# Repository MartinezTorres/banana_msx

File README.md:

# banana_msx

Building module:

banana_msx/kernel/module$ make ARCH=arm CROSS_COMPILE=arm-linux-gnueabihf-

Building kernel:

make ARCH=arm CROSS_COMPILE=arm-linux-gnueabihf- menuconfig zImage modules dtbs -j 4

make modules_install INSTALL_MOD_PATH=tmp_install

sudo update-initramfs -c -v -k 5.15.93

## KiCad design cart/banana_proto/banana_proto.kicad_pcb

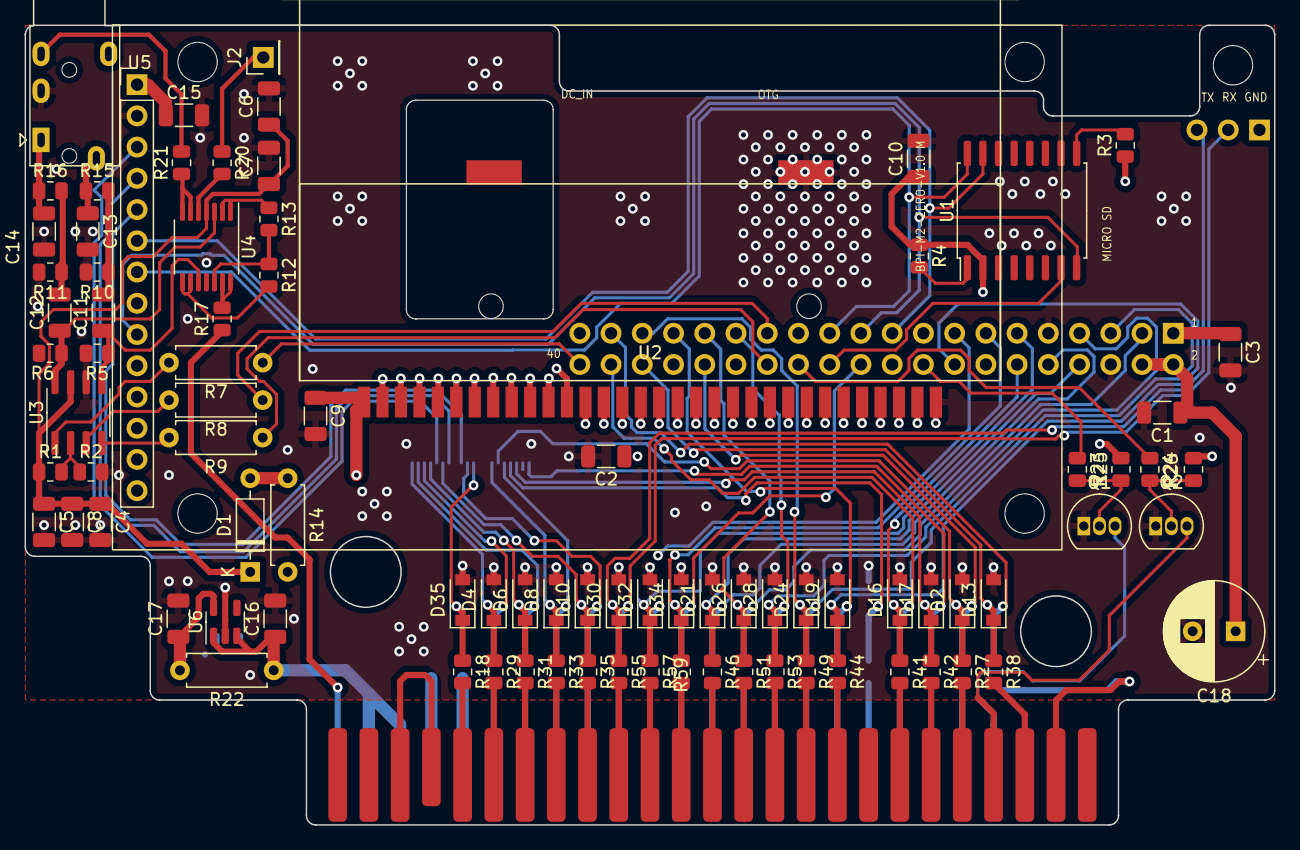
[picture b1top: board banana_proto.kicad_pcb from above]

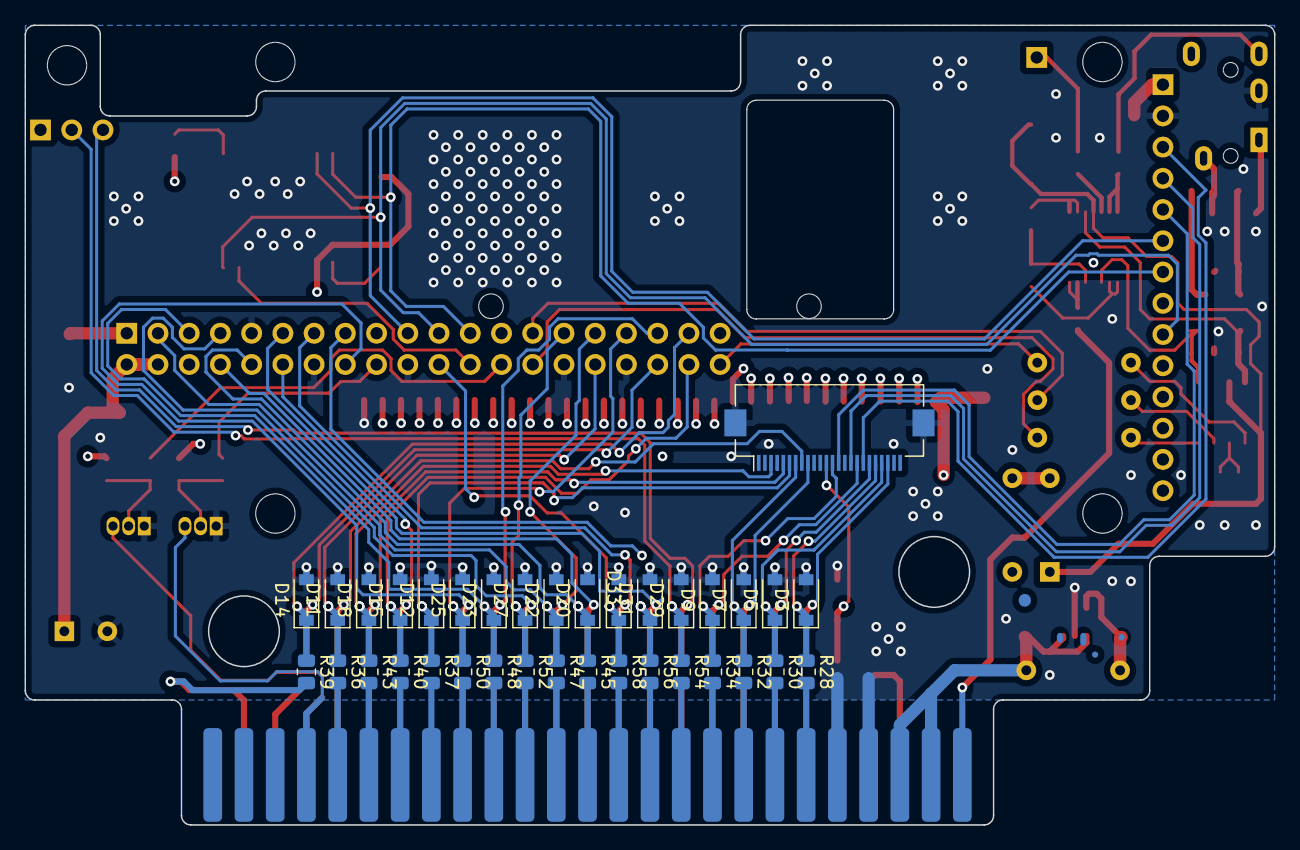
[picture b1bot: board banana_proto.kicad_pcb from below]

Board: 4 copper layers, 101.6 x 65.0 mm, 123 parts (34 on the bottom side), 112 nets.

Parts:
B1: Banana_PI_M2_Zero; BananaPI M2 Zero
BUS1: MSX_SLOT_EDGE-CON; msx_cartridge
C1, C2, C3, C5, C6, C9, C10, C15, C16, C17: 1uF; C_1206_3216Metric
C4: 10uF; C_1206_3216Metric
C7, C8: 0.1uF; C_1206_3216Metric
C11, C12: 3.3uF; C_1206_3216Metric
C13, C14: 10nF; C_1206_3216Metric
C18: 2200uF 6.3V; CP_Radial_D8.0mm_P3.50mm
D1: 1N6858; D_DO-35_SOD27_P7.62mm_Horizontal
D2, D3, D4, D5, D6, D7, D8, D9, D10, D11, D12, D13, D14, D15, D16, D17, D18, D19, D20, D21, D22, D23, D24, D25, D26, D27, D28, D29, D30, D31, D32, D33, D34, D35: BZT52C2V7-TP; D_SOD-123
J2: COMPOSITE; PinHeader_1x01_P2.54mm_Vertical
J3: AudioJack3_Ground; Jack_3.5mm_PJ320E_Horizontal
Q1, Q2: 2N3904; TO-92_Inline
R1, R2, R10, R11: 10k; R_0805_2012Metric
R3, R4, R18, R23, R24, R27, R28, R29, R30, R31, R32, R33, R34, R35, R36, R37, R38, R39, R40, R41, R42, R43, R44, R45, R46, R47, R48, R49, R50, R51, R52, R53, R54, R55, R56, R57, R58, R59: 330; R_0805_2012Metric
R5, R6: 267K; R_0805_2012Metric
R7, R8, R9, R14: 0; R_Axial_DIN0207_L6.3mm_D2.5mm_P7.62mm_Horizontal
R12, R13, R25, R26: 2K2; R_0805_2012Metric
R15, R16, R17: 560; R_0805_2012Metric
R20, R21: 75; R_0805_2012Metric
R22: 0 DNP; R_Axial_DIN0207_L6.3mm_D2.5mm_P7.62mm_Horizontal
U1: MT25QL01GBBB; SOIC-16W_7.5x10.3mm_P1.27mm
U2: CartBus; DSL_Cartridge_Reader
U3: CS4334; SOIC-8_3.9x4.9mm_P1.27mm
U4: MAX4395; TSSOP-14_4.4x5mm_P0.65mm
U5: ILI9341_TFT_LCD_Module; ILI9341 TFT LCD 24 modul
U6: NCP699SN50T1G; SOT-23-5

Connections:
+3V3: B1.P01 (VCC-3V3), B1.P17 (VCC-3V3), C2.1, C3.1, C10.1, C15.1, R3.1, R4.1, R25.2, R26.2, U1.2 (VCC), U5.1 (VCC), U5.8 (LCD_BACKGROUND)
+5V: B1.P02 (VCC-5V), B1.P04 (VCC-5V), C1.1, C9.1, C17.1, C18.1, R14.2, R22.2, U2.1 (VCC), U6.5 (OUT)
+5VA: C4.1, C5.1, C6.1, C7.1, C8.1, D1.1 (K), R1.1, U3.7 (VA), U4.4 (V+)
/A0: BUS1.28 (A0), R59.2
/A1: BUS1.27 (A1), R58.2
/A2: BUS1.30 (A2), R57.2
/A3: BUS1.29 (A3), R56.2
/A4: BUS1.32 (A4), R55.2
/A5: BUS1.31 (A5), R54.2
/A6: BUS1.22 (A6), R53.2
/A7: BUS1.21 (A7), R52.2
/A8: BUS1.24 (A8), R51.2
/A9: BUS1.17 (A9), R50.2
/A10: BUS1.20 (A10), R49.2
/A11: BUS1.19 (A11), R48.2
/A12: BUS1.23 (A12), R47.2
/A13: BUS1.26 (A13), R46.2
/A14: BUS1.25 (A14), R45.2
/A15: BUS1.18 (A15), R44.2
/COMPOSITE: J3.R2, R21.2
/D0: BUS1.34 (D0), R35.2
/D1: BUS1.33 (D1), R34.2
/D2: BUS1.36 (D2~), R33.2
/D3: BUS1.35 (D3), R32.2
/D4: BUS1.38 (D4), R31.2
/D5: BUS1.37 (D5), R30.2
/D6: BUS1.40 (D6), R29.2
/D7: BUS1.39 (D7), R28.2
/I2S_BCLK: B1.P27 (PA19), R8.1
/I2S_DOUT: B1.P40 (PA20), R7.1
/I2S_MCLK: B1.P28 (PA18), R9.1
/IRQ: B1.P26 (PC7), R24.1
/LCD_D/~C: B1.C14 (PE10), U5.5 (LCD_D/~C)
/LCD_~CS: B1.C18 (PE8), U5.3 (LCD_~CS)
/LCD_~RESET: B1.C16 (PE9), U5.4 (LCD_~RESET)
/SND: BUS1.49 (SOUNDOUT), R17.1
/SND_L_RAW: C12.1, R6.1, U3.8 (AOUTL), U4.3 (+)
/SND_R_RAW: C11.1, R5.1, U3.5 (AOUTR), U4.10 (+)
/SPI0_CLK: B1.P23 (PC2), U1.16 (SCK), U5.7 (LCD_SCK)
/SPI0_CS: B1.P24 (PC3), U1.7 (~CE)
/SPI0_MISO: B1.P21 (PC1), U1.8 (SO/IO1), U5.9 (LCD_MISO)
/SPI0_MOSI: B1.P19 (PC0), U1.15 (SI/IO0), U5.6 (LCD_MOSI)
/SPKR_L: C14.1, J3.T, R16.1
/SPKR_R: C13.1, J3.S, R15.1
/SW1: BUS1.44 (SW1), BUS1.46 (SW2)
/SYS_CLK: BUS1.42 (CLOCK), R18.2
/VIN: BUS1.45 (+5V), BUS1.47 (+5V), C16.1, R22.1, U6.1 (IN), U6.3 (EN)
/WAIT: B1.P18 (PC4), R23.1
/_A0: B1.P13 (PA0), D34.1 (K), R59.1
/_A1: B1.P22 (PA2), D33.1 (K), R58.1
/_A2: B1.P11 (PA1), D32.1 (K), R57.1
/_A3: B1.P15 (PA3), D31.1 (K), R56.1
/_A4: B1.S03 (PA4-TX), D30.1 (K), R55.1
/_A5: B1.S02 (PA5-RX), D29.1 (K), R54.1
/_A6: B1.P07 (PA6), D28.1 (K), R53.1
/_A7: B1.P29 (PA7), D27.1 (K), R52.1
/_A8: B1.P31 (PA8), D26.1 (K), R51.1
/_A9: B1.P33 (PA9), D25.1 (K), R50.1
/_A10: B1.P35 (PA10), D24.1 (K), R49.1
/_A11: B1.P05 (PA11), D23.1 (K), R48.1
/_A12: B1.P03 (PA12), D22.1 (K), R47.1
/_A13: B1.P08 (PA13), D21.1 (K), R46.1
/_A14: B1.P10 (PA14), D20.1 (K), R45.1
/_A15: B1.P16 (PA15), D19.1 (K), R44.1
/_D0: B1.C17 (PE0), D10.1 (K), R35.1
/_D1: B1.C13 (PE1), D9.1 (K), R34.1
/_D2: B1.C09 (PE2), D8.1 (K), R33.1
/_D3: B1.C07 (PE3), D7.1 (K), R32.1
/_D4: B1.C19 (PE4), D6.1 (K), R31.1
/_D5: B1.C21 (PE5), D5.1 (K), R30.1
/_D6: B1.C22 (PE6), D4.1 (K), R29.1
/_D7: B1.C20 (PE7), D3.1 (K), R28.1
/_~BUSDIR: B1.C08 (PE15), D2.1 (K), R27.1
/_~IORQ: B1.C03 (PE13), D18.1 (K), R43.1
/_~M1: B1.P32 (PL2), D11.1 (K), R36.1
/_~MERQ: B1.C05 (PE12), D17.1 (K), R42.1
/_~RD: B1.P12 (PA16), D16.1 (K), R41.1
/_~RESET: B1.C06 (PE14), D12.1 (K), R37.1
/_~RFSH: B1.P36 (PL4), D13.1 (K), R38.1
/_~SLTSL: B1.P37 (PA17), D14.1 (K), R39.1
/_~SYS_CLK: B1.C12 (PE11), D35.1 (K), R18.1
/_~WR: B1.P38 (PA21), D15.1 (K), R40.1
/~BUSDIR: BUS1.10 (~BUSDIR), R27.2
/~INT: BUS1.8 (~INT), Q2.3 (C)
/~IORQ: BUS1.11 (~IORQ), R43.2
/~M1: BUS1.9 (~M1), R36.2
/~MERQ: BUS1.12 (~MERQ), R42.2
/~RD: BUS1.14 (~RD), R41.2
/~RESET: BUS1.15 (~RESET), R37.2
/~RFSH: BUS1.6 (~RFSH), R38.2
/~SLTSL: BUS1.4 (~SLTSL), R39.2
/~WAIT: BUS1.7 (~WAIT), Q1.3 (C)
/~WR: BUS1.13 (~WR), R40.2
GND: B1.C02 (GND), B1.C15 (GND), B1.C23 (GND), B1.P06 (GND), B1.P09 (GND), B1.P14 (GND), B1.P20 (GND), B1.P25 (GND), B1.P30 (GND), B1.P34 (GND), B1.P39 (GND), BUS1.41 (GND), BUS1.43 (GND), C1.2, C2.2, C3.2, C4.2, C5.2, C6.2, C7.2, C8.2, C9.2, C10.2, C13.2, C14.2, C15.2, C16.2, C17.2, C18.2, D2.2 (A), D3.2 (A), D4.2 (A), D5.2 (A), D6.2 (A), D7.2 (A), D8.2 (A), D9.2 (A), D10.2 (A), D11.2 (A), D12.2 (A), D13.2 (A), D14.2 (A), D15.2 (A), D16.2 (A), D17.2 (A), D18.2 (A), D19.2 (A), D20.2 (A), D21.2 (A), D22.2 (A), D23.2 (A), D24.2 (A), D25.2 (A), D26.2 (A), D27.2 (A), D28.2 (A), D29.2 (A), D30.2 (A), D31.2 (A), D32.2 (A), D33.2 (A), D34.2 (A), D35.2 (A), J3.R1, Q1.1 (E), Q2.1 (E), R2.2, R5.2, R6.2, R10.2, R11.2, U1.10 (GND), U2.32 (GND), U3.6 (AGND), U4.11 (V-), U5.2 (GND), U6.2 (GND)
unnamed: C11.2, R10.1, R15.2
unnamed: C12.2, R11.1, R16.2
unnamed: D1.2 (A), R14.1
unnamed: J2.1, R20.1
unnamed: Q1.2 (B), R23.2, R25.1
unnamed: Q2.2 (B), R24.2, R26.1
unnamed: R1.2, R2.1, U3.2 (~DEM/SCLK)
unnamed: R3.2, U1.9 (~WP/IO2)
unnamed: R4.2, U1.1 (~HOLD/IO3)
unnamed: R7.2, U3.1 (SDATA)
unnamed: R8.2, U3.3 (LRCK)
unnamed: R9.2, U3.4 (MCLK)
unnamed: R12.1, R13.2, U4.12 (+)
unnamed: R12.2, U4.8, U4.9 (-)
unnamed: R13.1, U4.1, U4.2 (-)
unnamed: R17.2, U4.13 (-), U4.14
unnamed: R20.2, U4.5 (+)
unnamed: R21.1, U4.6 (-), U4.7

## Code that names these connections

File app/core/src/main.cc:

#include "h3.h"

enum {
	RD = 1<<16, // PA
	WR = 1<<21, // PA
	SLTSL = 1<<17, // PA

	LCD_CS = 1<<8, // PE
	LCD_RESET = 1<<9, // PE
	LCD_DC = 1<<10, // PE

	SYS_CLK = 1<<11, // PE
	MERQ = 1<<12, // PE
	IORQ = 1<<13, // PE
	RESET = 1<<14, // PE
	BUSDIR = 1<<15, // PE
	
	M1 = 1<<2, // PL
	RFSH = 1<<4, // PL

	WAIT = 1<<4, // PC
	IRQ = 1<<7, // PC
};

/*

struct {
	#define PIO                          0x01C20800
#define PA                           0x00
#define PE                           0x04
#define Pn_CFG0(reg)                 *((volatile u32 *)(PIO + reg*0x24 + 0x00))
#define Pn_CFG1(reg)                 *((volatile u32 *)(PIO + reg*0x24 + 0x04))
#define Pn_CFG2(reg)                 *((volatile u32 *)(PIO + reg*0x24 + 0x08))
#define Pn_CFG3(reg)                 *((volatile u32 *)(PIO + reg*0x24 + 0x0C))
#define Pn_DAT(reg)                  *((volatile u32 *)(PIO + reg*0x24 + 0x10))
#define Pn_DRV0(reg)                 *((volatile u32 *)(PIO + reg*0x24 + 0x14))
#define Pn_DRV1(reg)                 *((volatile u32 *)(PIO + reg*0x24 + 0x18))
#define Pn_DUL0(reg)                 *((volatile u32 *)(PIO + reg*0x24 + 0x1C))
#define Pn_DUL1(reg)                 *((volatile u32 *)(PIO + reg*0x24 + 0x20))

	// PA WILL BE MAPPED AS FOLLOWS:
	// PA0-15 - ADDRESS
	// PA16 - MREQ
	// PA17 - SLTSL
	// PA18 - CS
	// PC0  - WAIT
	// PA19 - WR
	// PA20 - RD

#define MREQ        (1<<16)	
#define SLTSL       (1<<17)	
#define CS          (1<<18)	
#define WR          (1<<19)	
#define RD          (1<<20)	
 




void ascii8_mapper(void) {

	//u8 *mapped_rom = (u8 *)0x58020000;
	u8 *mapped_zones[4] = {
		(u8 *)0x58020000,
		(u8 *)0x58022000,
		(u8 *)0x58024000,
		(u8 *)0x58028000};
		
	while (1) {
		u32 pa = Pn_DAT(PA);

		if ( ( pa & (MREQ + SLTSL + CS + RD) ) == 0 ) { // let's deal first with a read
			
			Pn_DAT(PE) = mapped_zones[(pa>>14) & 0x03][pa & 0x1FFF];
			Pn_CFG0(PE) = 0x11111111; // set PA7 to output;
			while ( ( Pn_DAT(PA) & CS ) == 0) {}
			Pn_CFG0(PE) = 0x00000000; // set PA7 to input;
			continue;
		}

		if ( pa & CS ) continue;
		if ( ( pa &  (MREQ + SLTSL + CS + WR) ) == 0 ) { // It's a write!
			u32 pe = Pn_DAT(PE);
			pa = pa & 0xF800;
			if (pa == 0x60) { mapped_zones[0] =  (u8 *)(0x58020000 + ( (pe & 0xFF) * 0x2000 ) ); }
			if (pa == 0x68) { mapped_zones[1] =  (u8 *)(0x58020000 + ( (pe & 0xFF) * 0x2000 ) ); }
			if (pa == 0x70) { mapped_zones[2] =  (u8 *)(0x58020000 + ( (pe & 0xFF) * 0x2000 ) ); }
			if (pa == 0x78) { mapped_zones[3] =  (u8 *)(0x58020000 + ( (pe & 0xFF) * 0x2000 ) ); }
		}
	}
}

	
} msx;
*/


static inline void set_cpu_speed() {
	
	H3.log.printf("Speed: %08x\n", H3.PLL_CPUX_CTRL_REG.DW );

//	H3.PLL_CPUX_CTRL_REG.DW = 0x90001410;
	H3.PLL_CPUX_CTRL_REG.DW = 0x90001810;
//	H3.PLL_CPUX_CTRL_REG.DW = 0x90000810;

	H3.log.printf("Speed: %08x\n", H3.PLL_CPUX_CTRL_REG.DW );
}

static inline void set_caches(bool enable_icache, bool enable_dcache) {
    uint32_t sctlr;
    asm volatile (
        "MRC p15, 0, %[sctlr], c1, c0, 0\n"  // Read the SCTLR into %[sctlr]
        : [sctlr] "=r" (sctlr)              // Define %[sctlr] as an output operand
        :                                   // No inputs
    );
    
    if (enable_icache) {
        sctlr |= (1 << 12); // Set bit 12 (the I-bit) to enable the instruction cache
        sctlr |= (1 << 11); // Set bit 11 to enable branch prediction
    } else {
        sctlr &= ~(1 << 12); // Clear bit 12 (the I-bit) to disable the instruction cache
        sctlr &= ~(1 << 12); // Clear bit 11 to disable branch prediction
    }
    
    if (enable_dcache) {
        sctlr |= (1 << 2); // Set bit 2 (the C-bit) to enable the data cache
    } else {
        sctlr &= ~(1 << 2); // Clear bit 2 (the C-bit) to disable the data cache
    }
    
    asm volatile (
        "MCR p15, 0, %[sctlr], c1, c0, 0\n"  // Write the modified SCTLR value back to the register
        "isb\n"
        "dsb\n"
        :                                   // No outputs
        : [sctlr] "r" (sctlr)               // Define %[sctlr] as an input operand
    );
}


static inline uint32_t read_sctlr() {
    uint32_t sctlr;
    asm volatile (
        "MRC p15, 0, %[sctlr], c1, c0, 0\n"  // Read the SCTLR into %[sctlr]
        : [sctlr] "=r" (sctlr)              // Define %[sctlr] as an output operand
        :                                   // No inputs
    );
    return sctlr;
}



#define UNROLL1(a) do { {a} } while (false)
#define UNROLL8(a) do { {a} {a} {a} {a} {a} {a} {a} {a} } while (false)


extern "C" void main() {

	
	//while (1);

	H3.log.init();
	H3.log << "Hello ";
	H3.log << " world ARM!\n";

	H3.log.printf("read_sctlr %08x\n", read_sctlr() );
	set_caches(false, false);
	H3.log.printf("read_sctlr %08x\n", read_sctlr() );
	set_caches(true, true);
	H3.log.printf("read_sctlr %08x\n", read_sctlr() );
	

	H3.AHB1_APB1_CFG_REG.DW = 0x3140;
	H3.CPUX_AXI_CFG_REG.DW = 0x20201;

	constexpr uint32_t N_ITER = 100000;
	constexpr uint32_t N_REP = 1;

	uint32_t t0 = H3.TMR1_CUR_VALUE_REG.DW;
	uint32_t v = 0;

	uint32_t i = N_ITER;
	while (i--) {
		UNROLL1({
			H3_T::io pa; pa.DW = H3.PA.DATA.DW;
			H3_T::io pe; pe.DW = H3.PE.DATA.DW;
			
			H3_T::io msx_control_bus = pa;
			msx_control_bus.byte3 = pe.byte1;
			
			if (msx_control_bus.bit15 && msx_control_bus.bit16) { 
				pe.bit04 = pa.bit05;
			}
			v += pe.DW;
			//H3.PE.DATA = pe;
		});
	}
	H3.AHB1_APB1_CFG_REG.DW = 0x3180;
	H3.CPUX_AXI_CFG_REG.DW = 0x20203;
	if (v == 0) {
		H3.log << "Done 2!\n";
	} else {
		H3.log << "Not Done 2!\n";
	}
	uint32_t t1 = H3.TMR1_CUR_VALUE_REG.DW;
	int d = t0 - t1;

	H3.log.printf(" %d %d %d \n", t0, t1, d);
	
	H3.log.printf("%d\n", d/(24 * N_REP * (N_ITER / 1000)));
	
	H3.log.printf("%08x\n", H3.CPUX_AXI_CFG_REG.DW );
	
	H3.log.printf("%08x\n", H3.AHB1_APB1_CFG_REG.DW );
	
	H3.log.printf("CPU_CLK_GATING_REG %08x\n", H3.CPU_CLK_GATING_REG.DW );
	
	
	H3.log.printf("CPU0_RST_CTRL %08x\n", H3.CPU0_RST_CTRL.DW );
	H3.log.printf("CPU0_CTRL_REG %08x\n", H3.CPU0_CTRL_REG.DW );
	H3.log.printf("CPU0_STATUS_REG %08x\n", H3.CPU0_STATUS_REG.DW );
	
	H3.log.printf("CPU3_RST_CTRL %08x\n", H3.CPU3_RST_CTRL.DW );
	H3.log.printf("CPU3_CTRL_REG %08x\n", H3.CPU3_CTRL_REG.DW );
	H3.log.printf("CPU3_STATUS_REG %08x\n", H3.CPU3_STATUS_REG.DW );

	
}

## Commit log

2023-04-06 initial
2023-04-12 keep improving stuff
2023-04-12 original linux code
2023-04-12 small modification to the kernel source to enable bare metal on core 3
2023-04-12 adding configuration
2023-04-13 jar jar accessing raw memory!
2023-04-13 splitting core
2023-04-16 problems when compiling
2023-04-19 runded connector
2023-04-20 pcb almost ready
2023-04-27 updated hal
2023-05-03 working on hypervisor stub
2023-05-05 seems quite nice
2023-05-05 scad
2023-05-09 updated app and cart
